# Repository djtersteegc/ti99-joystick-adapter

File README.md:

TI-99/4A joystick adapter allowing for the use of two standard Atari style DB9 joysticks.  BOM is super simple, I used these DB9's from AliExpress (similar to a TE [2301826-2](https://www.te.com/usa-en/product-2301826-2.html) and [2301838-2](https://www.te.com/usa-en/product-2301838-2.html) )

https://www.aliexpress.us/item/2255799921187046.html

and some LL4148 diodes in a MiniMELF form factor

https://www.aliexpress.us/item/3256802562651339.html

The top of the 4-40 lugs simply unscew from the DB9 sockets leaving the bottom part to securly mount to the PCB.

There is a snapfit 3D printable case in the **enclosure** directory.  Prints fine without any sort of supports, clearances are 0.2mm which work well on my Ender 3 style printer when printed in standard PLA. I included the DesignSpark file and STEP export of the populated board if you would like to improve on it further.

In the **gerbers** directory there is also a panelized version that will produce six boards on a standard 100x100mm PCB.  That was before JLCPCB started charging more for panelized design, so use at your your own (financial) risk these days.

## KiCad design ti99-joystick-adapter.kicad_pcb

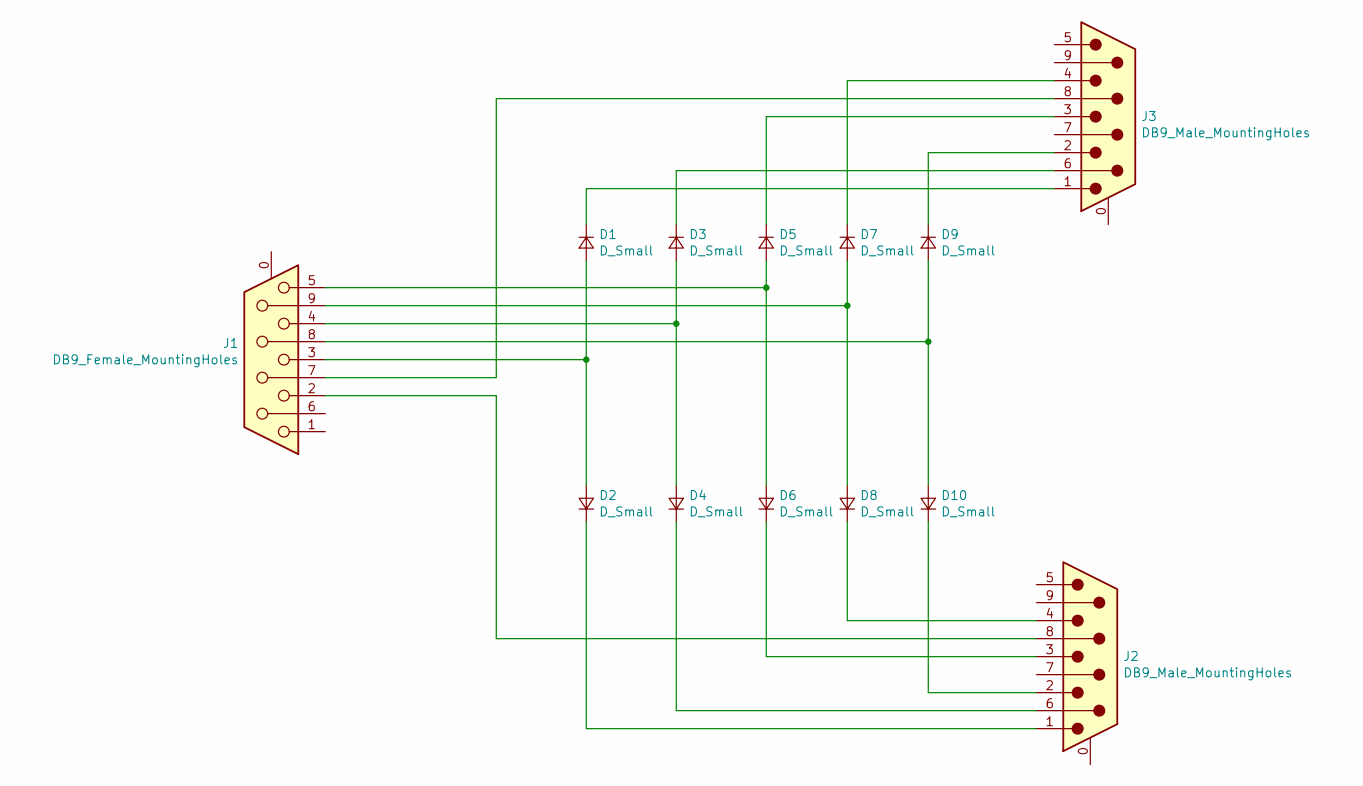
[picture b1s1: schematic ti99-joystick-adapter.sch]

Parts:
D1, D2, D3, D4, D5, D6, D7, D8, D9, D10: D_Small; D_MiniMELF_Handsoldering
J1: DB9_Female_MountingHoles; DSUB-9_Female_Vertical_P2.77x2.84mm_MountingHoles
J2, J3: DB9_Male_MountingHoles; DSUB-9_Male_Vertical_P2.77x2.84mm_MountingHoles

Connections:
unnamed: D1.1 (K), J3.1
unnamed: D1.2 (A), D2.2 (A), J1.3
unnamed: D2.1 (K), J2.1
unnamed: D3.1 (K), J3.6
unnamed: D3.2 (A), D4.2 (A), J1.4
unnamed: D4.1 (K), J2.6
unnamed: D5.1 (K), J3.3
unnamed: D5.2 (A), D6.2 (A), J1.5
unnamed: D6.1 (K), J2.3
unnamed: D7.1 (K), J3.4
unnamed: D7.2 (A), D8.2 (A), J1.9
unnamed: D8.1 (K), J2.4
unnamed: D9.1 (K), J3.2
unnamed: D10.1 (K), J2.2
unnamed: D9.2 (A), D10.2 (A), J1.8
unnamed: J1.2, J2.8
unnamed: J1.7, J3.8

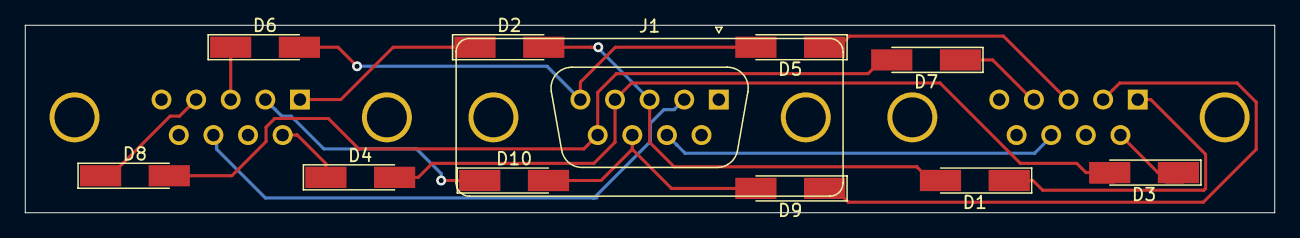
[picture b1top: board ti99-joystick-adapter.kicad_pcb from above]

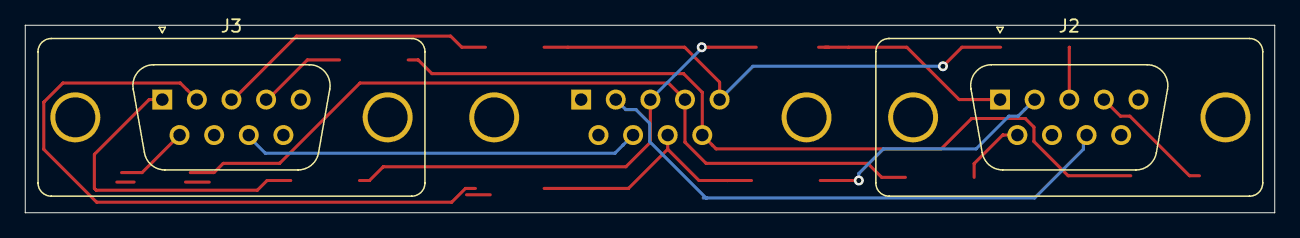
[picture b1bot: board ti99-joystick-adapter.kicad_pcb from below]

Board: 2 copper layers, 100.0 x 15.0 mm, 13 parts (2 on the bottom side), 17 nets.

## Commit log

2021-02-28 Initial version set to JCL
2022-05-03 Add new files
2022-11-08 Fixup 3D models
2022-11-08 Add enclosure
2022-11-08 Fix README
